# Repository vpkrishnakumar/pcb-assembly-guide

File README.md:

<h1 align="center">PCB Assembly Guide</h1>

<p align="center">
  A Mac app that walks you through hand-soldering a KiCad board, one part at a time, on a 3D view of the real board.
</p>

<p align="center">

</p>

Open a `.kicad_pcb` file and the app shows you which part to pick up, where it goes and which way round. Press Space when it is soldered and it moves to the next one.

It reads the board file directly, so there is no BOM export, plugin or position file to prepare. It never writes to your KiCad project.

## Features

- **3D board, one part at a time.** The board is rendered with KiCad's own 3D models. The part to place is ringed in green and the camera moves to it. Parts already soldered stay on the board, so the screen matches what is on your bench.
- **Big value and package.** The value (`470R`, `100nF`) and size (`0402`, `QFN-32`) are shown large enough to read from across the bench, with the body dimensions in millimetres.
- **Polarity and pin 1.** Diodes, LEDs, polarised capacitors and ICs get a red dot on the board at the cathode, positive pad or pin 1, plus a plain-language note on how to find that mark on the part. Parts that fit either way round say so.
- **Kit list first.** A new board opens on a pick list with the quantity of every value, so you can take the right number of each part before you start.
- **Sensible order.** Surface-mount before through-hole, ICs first, then small to large. Identical parts are grouped and walked in a short path across the board. Pick another preset or drag groups into your own order.
- **Flat view.** A top-down view that matches the silkscreen drawing, for when the perspective view is harder to read.
- **Both sides.** The board turns over for bottom-side parts.
- **Marking hints.** Shows the code printed on a resistor (`471`, `4700`) and warns when a part is normally unmarked.
- **Jumper links.** For three-pad solder jumpers with a value such as `0R (pads 2-3)`, the two pads to bridge are highlighted.
- **Connections.** Lists the nets on each pad, so you can check a joint with a multimeter.
- **Search and click.** Find any part by reference, value or package, or click it on the 3D board to jump to it.
- **Notes and flags.** Mark a part as out of stock, needing rework or substituted, and review them all on the Notes tab.
- **Several boards.** Build a batch from one design. Progress and notes are kept per physical board.
- **Bench display.** A second window with very large type for a spare monitor.
- **Hands-free stepping.** Space, Return, arrow keys and Page Up/Down all work, so a foot pedal or presenter clicker does too.
- **Voice control (experimental).** Say "next", "back" or "skip". This has had little testing; please report problems.
- **Progress is saved.** Close the app mid-board and it reopens where you stopped.
- **KiCad plugin.** A toolbar button in KiCad's PCB editor makes the web guide for the open board. See [KiCad plugin](#kicad-plugin).
- **Web guide export.** Save the whole guide as one HTML file and send it to anyone. It opens in any browser on any device, with no app and no KiCad. See [Sharing a guide](#sharing-a-guide).

## Screenshots

| | |
|---|---|
|  **Kit** shows how many of each part to take |  **Polarity** marks the cathode in red |
|  **Resistors** show the printed code |  **Flat view** matches the silkscreen |
|  **Order** can be rearranged by dragging |  **Bench display** for a second screen |

The board in the screenshots is the [RoyalBlue54L Feather](https://github.com/Lords-Boards/RoyalBlue54L-Feather) by Lord's Boards, one of KiCad's demo projects, released under CERN-OHL-P v2.

## Requirements

- macOS 14 (Sonoma) or later.
- [KiCad](https://www.kicad.org/download/macos/) installed in `/Applications`. The app uses KiCad's `kicad-cli` to export the board's 3D model and reads KiCad's standard 3D model library. It was developed against KiCad 10.
- To build: the Swift toolchain, either from Xcode or the Command Line Tools (`xcode-select --install`). Xcode itself is not needed.

Without KiCad the app still opens a board and guides you through it, but it draws a plain slab with boxes for the parts.

## Build and install

```sh
git clone https://github.com/vpkrishnakumar/pcb-assembly-guide.git
cd pcb-assembly-guide
./build.sh install
```

`./build.sh` builds `build/PCB Assembly Guide.app`. Adding `install` also copies it to `/Applications`.

The app is ad-hoc signed. If you copy a build to another Mac, right-click it and choose Open the first time.

## Linux and Windows

The Mac app's window does not run on other systems, but the guide does. A small command-line tool reads the board and writes the same web guide, then opens it in your browser:

```sh
git clone https://github.com/vpkrishnakumar/pcb-assembly-guide.git
python3 pcb-assembly-guide/cli/pcb_assembly_guide.py my-board.kicad_pcb
```

It needs Python 3.8 or later and nothing else: no packages to install. On Windows use `py` instead of `python3`.

With KiCad 8 or later installed, the page shows the board in 3D. The tool looks for `kicad-cli` on your `PATH`, then in the usual install locations (including the snap and Flatpak packages). If yours is somewhere else, set `KICAD_CLI=/path/to/kicad-cli`. Without KiCad you still get the full guide, with parts drawn as simple boxes.

| Option | Effect |
|---|---|
| `-o guide.html` | Where to write the page. The default is `<board>-assembly-guide.html` in the current folder. |
| `--order top-first` | Soldering order: `smd-first` (default), `top-first`, `bottom-first` or `smallest-first`. |
| `--no-3d` | Skip the KiCad export and draw simple boxes. |
| `--no-fill` | Do not borrow KiCad library models for chip parts that have none. |
| `--no-open` | Do not open the browser afterwards. |

The tool never writes into your KiCad project; exports are cached in `~/.cache/pcb-assembly-guide`.

It runs on macOS too, and produces the same page as the app's **Export Web Guide**. Automated tests check that the two agree.

## KiCad plugin

The same guide is one click away inside KiCad. The plugin adds an **Assembly Guide** button to the PCB editor's toolbar; it asks for the soldering order and where to save the page, then opens the guide in your browser. It works on macOS, Linux and Windows.

To install it:

1. Download `pcb-assembly-guide-kicad-plugin-<version>.zip` from the [latest release](https://github.com/vpkrishnakumar/pcb-assembly-guide/releases/latest). To build it yourself, run `python3 kicad-plugin/package.py`; it is written to `build/`.
2. In KiCad's main window open **Plugin and Content Manager**, choose **Install from File…** and pick the zip.
3. Open a board in the PCB editor. The button is on the top toolbar, and under **Tools > External Plugins**.

The guide is made from the board file as last saved, and the page is the only file the plugin writes. The plugin uses KiCad's older Python plugin interface, which KiCad 10 still supports; it has been tried with KiCad 10 on macOS only so far.

## Using it

1. Open a `.kicad_pcb` file with the folder button, **File > Open Board…** (⌘O), or by dragging it onto the window. The first load takes a few seconds while KiCad exports the 3D model. Later loads use a cache.
2. On the **Kit** tab, take the listed quantity of each part and tick each line off. Then choose **Start Assembling**.
3. On the **Assemble** tab, place the ringed part and press Space. Repeat.

### Keys

| Key | Action |
|---|---|
| Space, Return, Page Down | Part placed, go to the next |
| ←, Page Up | Go back one part |
| → | Skip this part for now |
| ⌘1 to ⌘4 | Assemble, Kit, Order, Notes |
| ⇧⌘F | Flat view |
| ⌘B | Bench display |
| ⇧⌘E | Export web guide |
| ⌘O | Open a board |

Drag on the 3D view to orbit, scroll to zoom, and click a part to jump to it.

### Sharing a guide

**File > Export Web Guide…** (⇧⌘E) writes a single `.html` file containing the 3D board, the step-by-step plan, the kit list and the polarity notes. Email it, put it on a shared drive or host it anywhere. The person building the board opens it in a browser on a Mac, Windows or Linux PC, a tablet or a phone. Nothing is installed and the page works offline.

| Desktop browser | Phone |
|---|---|
|  |  |

The page has the Assemble and Kit views, search, click-to-jump, flat view and the same keys as the app. Progress is saved in that browser. Notes, batches of several boards, custom ordering and voice control are only in the Mac app.

The file is usually 5 to 15 MB, because the board's 3D model is inside it. The 3D view uses [three.js](https://threejs.org) (MIT), which is bundled into the page.

From the command line:

```sh
.build/release/PCBAssemblyGuide --export-web board.kicad_pcb guide.html
```

### What gets assembled

Footprints marked *Do not populate*, *Exclude from BOM* or *Board only* are left out, as are footprints with no pads.

### Parts without a 3D model

If a two-pad resistor, capacitor, inductor, ferrite, diode or LED has no 3D model assigned, the app borrows the matching model from KiCad's standard library, working on a private copy of the board. Other parts without a model are drawn as boxes the size of their footprint. You can turn the borrowing off under the gear menu.

## How it works

1. **Parse.** `SExpr.swift` and `KiCadBoard.swift` read the `.kicad_pcb` S-expressions into components with their position, side, pads, nets and schematic pin functions.
2. **Work out polarity.** The cathode, positive pad or pin 1 comes from the schematic pin function stored on each pad (`K`, `A`, `+`), falling back to pad 1.
3. **Export.** `BoardLoader.swift` runs `kicad-cli pcb export glb` and caches the result in `~/Library/Caches/PCBAssemblyGuide`. KiCad names each node in the export after its reference, which is how the app can show and hide individual parts.
4. **Render.** `GLB.swift` loads the export into SceneKit, and `BoardScene.swift` handles visibility, the highlight ring, the polarity marker and the camera.
5. **Plan.** `AssemblyPlan.swift` groups and orders the parts.

The interface is SwiftUI (`Views.swift`) driven by one observable model (`AppModel.swift`). The app itself has no third-party dependencies. The exported web guide (`WebExport.swift`, `Resources/web/guide.html`) inlines three.js.

### Command-line mode

The binary can render a step without opening a window, which is useful for checking a board:

```sh
.build/release/PCBAssemblyGuide --snapshot board.kicad_pcb out.png 12          # step 12
.build/release/PCBAssemblyGuide --snapshot board.kicad_pcb out.png U3 --flat   # the step for U3, flat view
.build/release/PCBAssemblyGuide --snapshot board.kicad_pcb out.png all --list  # whole board, and print the plan
```

## Known limitations

- Polarity comes from the schematic and footprint, not from the physical part. Always confirm against the datasheet for anything expensive or unfamiliar. In particular, a TVS diode drawn with a cathode in the schematic is marked as polarised even if the fitted part is bidirectional.
- Switches and some connectors get no orientation mark.
- IC top markings are not predicted; the app links to the datasheet instead.
- Voice control is experimental.
- The Mac app is developed and tested on Apple Silicon with KiCad 10 only.
- On Linux and Windows the guide runs in the browser; there is no native window. Notes, batches of boards, drag-to-reorder and voice control are Mac-only.
- The KiCad plugin makes the web guide; it does not embed the Mac app's window in KiCad. KiCad plans to retire the plugin interface it uses, and the plugin will need porting to the newer one when that happens.
- The Flatpak and snap KiCad packages are detected but have had little testing.

## Contributing

Issues and pull requests are welcome. If a board loads wrongly, a small `.kicad_pcb` that reproduces it helps most.

The board parsing, polarity and ordering logic exists twice: in Swift for the Mac app and in `cli/pcb_assembly_guide.py` for other systems. A change to one needs the same change in the other; the build checks that both write the same guide for `tests/fixtures/sample.kicad_pcb`. Run the tests with `python3 -m unittest discover -s tests`. The KiCad plugin (`kicad-plugin/`) is a thin dialog around the same Python file, which `package.py` copies into the plugin archive.

Note for contributors building without Xcode: the Command Line Tools do not ship the SwiftUI macro plugin, so `@State` does not compile. View state lives in `AppModel` as `@Published` properties for that reason.

## Licence

[MIT](LICENSE).

KiCad is a trademark of the KiCad project. This app is not affiliated with or endorsed by KiCad.

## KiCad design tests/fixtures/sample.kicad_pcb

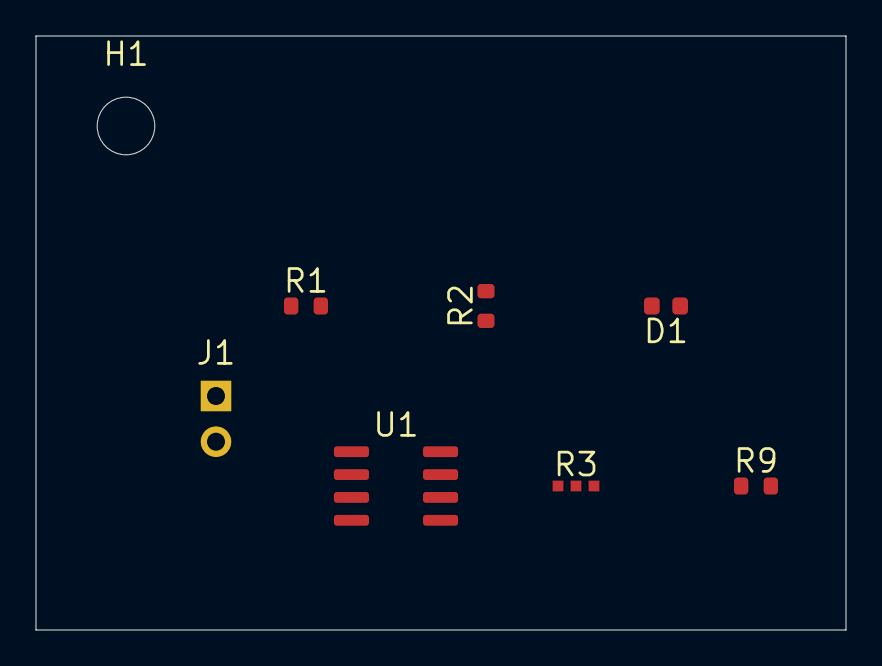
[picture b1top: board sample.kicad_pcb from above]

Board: 2 copper layers, 45.0 x 33.0 mm, 9 parts (1 on the bottom side), 3 nets, no tracks yet.

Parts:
C1: 100nF; C_0402_1005Metric
D1: GREEN; LED_0603_1608Metric
H1: M3 (not "soldered"); MountingHole_3.2mm_M3
J1: PWR; PinHeader_1x02_P2.54mm_Vertical
R1, R2: 10k; R_0603_1608Metric
R3: 0R (pads 2-3); RC-0402-Jumper
R9: 4k7; R_0603_1608Metric
U1: OPAMP; SOIC-8_3.9x4.9mm_P1.27mm

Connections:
GND: C1.2, D1.1 (K), J1.2, R2.2, R9.2, U1.4
unnamed: D1.2 (A), R1.2
VCC: C1.1, J1.1, R1.1, R2.1, R9.1, U1.8
